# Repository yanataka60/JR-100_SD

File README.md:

# National JR-100にSD-CARDとのロード、セーブ機能

　JR-100でSD-CARDからPROG形式ファイルのロード、セーブ機能を実現するものです。

　CMTからの読み込み実行に数分掛かっていたゲームも数十秒で実行できます。

　接続は、JR-100本体後ろの拡張端子に直接挿して使います。

　なお、Arduino、ROM、GALへ書き込むための機器が別途必要となります。

　オプションとしてジョイスティックポート、拡張RAM($4000～$7FFF)も装備できます。

### 2025.2.26 PIOに6821を使ったRev2.1ではPIOアクセス時の画面ノイズが発生しないので6821版を正式版とし、8255版は8255フォルダに移動しました。なお、開発に使用した3台のJR-100では6821版、8255版ともに安定動作していますが、8255版は動作不安定であると報告された機体でも6821版は安定動作しているとの動作報告がありました。

## 回路図
　KiCadフォルダ内のJR-100_SD.pdfを参照してください。

[回路図](https://github.com/yanataka60/JR-100_SD/blob/main/Kicad/JR-100_SD.pdf)

## 部品
|番号|品名|数量|備考|
| ------------ | ------------ | ------------ | ------------ |
|J1(J2)|50Pカードエッジコネクタ|1|せんごくネット通販 HRS CR22A-50D-2.54DSなど|
|J4|コネクタ 2Pin|1|ピンヘッダで代用するときはGNDと間違えないよう1Pinで5Vだけにしたほうが良い|
|J5|DCジャック|1|秋月電子通商 MJ-179PHなど|
||J6、J7のいずれか|||
|J6|Micro_SD_Card_Kit|1|秋月電子通商 AE-microSD-LLCNV (注1) (注2)|
|J7|MicroSD Card Adapter|1|Arduino等に使われる5V電源に対応したもの (注2)|
|U1|GAL22V10|1||
|U3|ROM 2764/28C64相当品|1||
|U5|6821|1|若松通商 HD46821P等|
|U6|Arduino_Pro_Mini_5V|1|Atmega328版を使用 168版は不可。(注3)|
|C1,C2,C5|積層セラミックコンデンサ 0.1uF|3||
|C6|電解コンデンサ 16v100uF|1||
|S1|3Pスライドスイッチ|1|秋月電子通商 SS12D01G4など|
||ピンヘッダ|2Pin分|Arduino_Pro_MiniにはA4、A5用のピンヘッダが付いていないため別途調達が必要です 秋月電子通商 PH-1x40SGなど|
||ピンソケット(任意)|26Pin分|Arduino_Pro_Miniを取り外し可能としたい場合に調達します 秋月電子通商 FHU-1x42SGなど|

JR-100_SDに外部から電源を供給する場合
|番号|品名|数量|備考|
| ------------ | ------------ | ------------ | ------------ |
||ACアダプター 5V|1|秋月電子通商 M050200-A010JPなど|

RAM($4000～$7FFF)を拡張する場合
|番号|品名|数量|備考|
| ------------ | ------------ | ------------ | ------------ |
|U4|RAM 62256相当品|1||
|C3|積層セラミックコンデンサ 0.1uF|1||

ジョイスティックポートを付ける場合
|番号|品名|数量|備考|
| ------------ | ------------ | ------------ | ------------ |
|J3|D-SUB 9Pオス基板取付型|1|マルツ 3223DB9RP1S2など|
|U2|74LS366|1||
|C4|積層セラミックコンデンサ 0.1uF|1||
|R1-R5|10KΩ|5||

リセットスイッチを使う場合
|番号|品名|数量|備考|
| ------------ | ------------ | ------------ | ------------ |
|SW1|タクトスイッチ|1|秋月電子通商 DTS-63-N-Vなど|
|J8|コネクタ 1Pin|1|リセット用ご自分の環境に合わせてください|

　　　注1)秋月電子通商　AE-microSD-LLCNVのJ1ジャンパはショートしてください。

　　　注2)J6又はJ7のどちらかを選択して取り付けてください。

### 　　注3)Arduino Pro MiniはA4、A5ピンも使っています。

### MicroSD Card Adapterを使う
　J7に取り付けます。

　MicroSD Card Adapterについているピンヘッダを除去してハンダ付けするのが一番確実ですが、J4の穴にMicroSD Card Adapterをぴったりと押しつけ、裏から多めにハンダを流し込むことでハンダ付けをする方法もあります。なお、この方法の時にはしっかりハンダ付けが出来たかテスターで導通を確認しておいた方が安心です。

　ハンダ付けに自信のない方はJ2の秋月電子通商　AE-microSD-LLCNVをお使いください。AE-microSD-LLCNVならパワーLED、アクセスLEDが付いています。

## ROMへの書込み
　ROMフォルダ内のSD.binをROMライター(TL866II Plus等)を使って2764又は28C64に書き込みます。

　2764(8KByteROM)を使っていますが、JR-100_SDからアクセスされるのは4KByte分です。

## Arduinoプログラム
　Arduino IDEを使ってArduinoフォルダのJR-100_SDフォルダ内JR-100.inoを書き込みます。

　SdFatライブラリを使用しているのでArduino IDEメニューのライブラリの管理からライブラリマネージャを立ち上げて「SdFat」をインストールしてください。

　「SdFat」で検索すれば見つかります。「SdFat」と「SdFat - Adafruit Fork」が見つかりますが「SdFat」のほうを使っています。

注)Arduinoを基板に直付けしている場合、Arduinoプログラムを書き込むときは、JR-100本体とは接続を外し、GAL22V10を外したうえで書き込んでください。

## GALへの書込み
　Wincuplフォルダ内のJR100.jedをROMライター(TL866II Plus等)を使ってGAL22V10に書き込みます。

#### ~~2025.1.20 8255が正常にアクセスできない個体があると報告がありましたので修正しました。以前のプログラムで正常に動作していれば書き込み直す必要はありません。~~

## 接続
　JR-100本体後ろの拡張端子に挿し込みます。

.jpg)

## 電源の供給
　JR-100の拡張端子には+5Vが出ていないため、JR-100_SDには別途電源を供給する必要があります。

　私は純正の電源アダプタではなく、別に入手したスイッチング電源を使用しているため、内部電源として本体内の+5Vが供給されているピンから線を引き出してJR-100_SDに供給しています。

　純正の電源アダプタを使用している方が内部から+5Vを引き出し内部電源としてJR-100_SDへ供給する場合、もしかすると電力不足で誤動作するかもしれません。

　もし、動作異常が起こるようであれば別に5V電源アダプタを用意し、外部電源として供給してください。

#### 2025.1.20 純正の電源アダプタを借りて試したところ、内部から引き出した+5Vで問題なく動作しました。

## リセットスイッチ
　リセットスイッチはJ8コネクタに接続された信号線をGNDに落とすためだけのスイッチです。

　リセットスイッチとして利用するためには、本体内部からリセット用の信号線を引き出してくる必要があります。

　引き出し方についてはWeb等で調べてください。

## SD-CARD
　出来れば8GB以下のSDカードを用意してください。

　ArduinoのSdFatライブラリは、SD規格(最大2GB)、SDHC規格(2GB～32GB)に対応していますが、SDXC規格(32GB～2TB)には対応していません。

　また、SDHC規格のSDカードであっても32GB、16GBは相性により動作しないものがあるようです。

　FAT16又はFAT32が認識できます。NTFSは認識できません。

　ルートに置かれた拡張子が「.PRG」のPROG形式ファイルのみ認識できます。(PROG形式以外のファイル、フォルダも表示されますがLOADの対象になりません)

　ファイル名は「.PRG」を含めて31文字まで、ただし半角カタカナ、及び一部の記号はArduinoが認識しないので使えません。パソコンでファイル名を付けるときはアルファベット、数字および空白でファイル名をつけてください。

## PROG形式
　けむしろうさん作JR-100エミュレータver2で採用されているファイル形式です。

https://yorumomiji.sakura.ne.jp/contents/jr-100-emulator

　PROG形式の詳細については、ページ中ほどの「JR-100エミュレータver2ユーザーズガイド」から「ファイル形式」「PROG形式」を参照してください。

　ただし、現在公開されているJR-100エミュレータver2.4.0は、PROG形式フォーマットバージョン2が採用されておりフォーマットバージョン1と互換性がありません。

　JR-100_SDではフォーマットバージョン1に対応、フォーマットバージョン2は単一セクションのみのPRGファイル読み込みだけ対応しています。

#### 注)複数セクションが含まれるフォーマットバージョン2 PRGファイルは読み込ませないでください。最初のセクションの読込が終了した後、Arduinoは次のセクションを送出しようとして待機状態となり、電源を入れ直すか、RESETするまで正常に動作しなくなります。

　エミュレータで使う本体ROMデータはPROG形式フォーマットバージョン1で動作しますのでJR-100_SDからMSAVEすれば簡単に作成できます。

## 使い方

### JR-100_SDの準備
　JR-100を起動したらHCOPYコマンド(CTRL+B)を実行します。

　「JR-100_SD READY OK!」と表示されたらSD-CARDにアクセスできます。

　もう一度HCOPYコマンド(CTRL+B)を実行すると「CMT READY OK!」と表示されCMTに戻ります。

　HCOPYコマンド(CTRL+B)を実行する度にJR-100_SDとCMTが切り替わります。

### BASICコマンド

　~SDへのアクセス中に画面にノイズが出ますが、異常ではありません。ノイズが出ないようにする方法が不明なためそのままにしてあります。~(2025.2.20 PIOを6821にすることで解消されました。)

#### SDDIR[CR]又はSDDIR "文字列"[CR]
　SDDIR[CR]とするとSD-CARDルートディレクトリにあるファイルの一覧を表示します。

　SDDIR "文字列"[CR]とするとSD-CARDルートディレクトリにあるその文字列から始まるファイルの一覧を表示します。

　10件表示したところで指示待ちになるので打ち切るならRETURNを入力すると打ち切られ、Bキーで前の10件に戻ります。それ以外のキーで次の10件を表示します。

　LOADしたいファイルを見つけたら左端の数字のキーを押せばLOADされます。

　BASICプログラムか、機械語プログラムかは自動で判断します。

　表示される順番は、登録順となりファイル名アルファベッド順などのソートした順で表示することはできません。

#### LOAD "DOSファイル名"[CR]
　指定したDOSフィル名のプログラムをSD-CARDからLOADします。

　BASICプログラムか、機械語プログラムかは自動で判断し、どちらをLOADしているかメッセージに表示します。

　また、機械語プログラムのLOAD時には読み込み開始アドレス、読み込み終了アドレスも表示されます。

　MLOADコマンドは使えませんのでLOADコマンドを使用してください。

　ファイル名の最後の「.PRG」も有っても無くても構いません。

　例)

　　LOAD "TEST" -> DOSファイル名「TEST.PRG」を読み込みます。

　　LOAD "TEST.BAS" -> DOSファイル名「TEST.BAS.PRG」を読み込みます。

　　LOAD "TEST.BAS.CMT" -> DOSファイル名「TEST.BAS.PRG」を読み込みます。

#### MEXEC[CR]
　機械語プログラムをLOADした後、A=USR($xxxx)[CR]として機械語プログラムを実行する代わりに実行アドレスが読み込み開始アドレスと同じ場合にはMEXEC[CR]とすることで機械語プログラムを実行できます。

#### SAVE "DOSファイル名"[CR]
　BASICプログラムを指定したDOSフィル名でSD-CARDに上書きSAVEします。

　ファイル名の省略は出来ません。

　ファイル名の最後の「.PRG」は有っても無くても構いません。

　指定したDOSファイル名の最初の16文字がPROG形式の中に保存されるファイル名として使われます。

　BASICプログラムであることを識別するためDOSファイル名に「.BAS」を含ませることを推奨します。

　例)

　　SAVE "TEST" -> 「TEST.PRG」で保存される。

　　SAVE "TEST.BAS" -> 「TEST.BAS.PRG」で保存される。

#### MSAVE "DOSファイル名",$xxxx,$yyyy[CR]
　16進数4桁で指定する$xxxxから$yyyyまでの機械語プログラムを指定したDOSフィル名でSD-CARDに上書きSAVEします。

　ファイル名の省略は出来ません。

　ファイル名の最後の「.PRG」は有っても無くても構いません。

　指定したDOSファイル名の最初の16文字がPROG形式の中に保存されるファイル名として使われます。

　機械語プログラムであることを識別するためDOSファイル名に「.BIN」を含ませることを推奨します。

　例)

　　MSAVE "TEST",$E000,$FFFF -> 「TEST.PRG」で保存される。

　　MSAVE "TEST.BIN",$E000,$FFFF -> 「TEST.BIN.PRG」で保存される。

#### A=USR($DF00)[CR]【メモリテスト】
　RAMをテストします。

　アドレス$0246からエラーが発生するまでRAMに$55を書き込み、$55が読みだせるか、次に$AAを書き込み、$AAが読みだせるか、テストを行います。

　RAMにエラーが無い場合、拡張RAMを実装していなければ$4000、拡張RAMを実装していれば$8000でエラーとなり終了します。

　それ以外のアドレスで停止すればそのアドレスに問題があります。

#### A=USR($DE00,$xxxx)[CR]【メモリダンプ】
　16進数4桁で指定するアドレス$xxxxから64Byte分のメモリをダンプします。

　64Byte表示したところで指示待ちになるので次の64Byteを表示するならSPACEキー又はNキー、前の64Byteを表示するならBキー、それ以外のキーでBASICに戻ります。

#### A=USR($DD00,$xxxx)[CR]【メモリエディット】
　16進数4桁で指定するアドレス$xxxxからメモリに書き込みます。

　アドレス$xxxxを表示して指示待ちになるので書き込みたいデータを16進数で入力してください。

　止めたい時はRETURNキーを押せばBASICに戻ります。

## I/Oポートのデコードについて
　JR-100_SDにおいてジョイスティックポート、6821(8255)、拡張RAM、拡張ROMのアドレスデコードはすべてGAL22V10で行っていますが、ピン数の関係で16Bitすべてのアドレス線をデコードすることが出来ていません。

　拡張RAM、拡張ROMのアドレスデコードに問題はありませんが、ジョイスティックポート、6821(8255)は以下の扱いになります。

　ジョイスティックポート回路の参考にさせていただいた「にがMSX～JR-100用ジョイスティックインターフェイスの製作～」ではジョイスティックIOは$CC02となっていますが、JR-100_SDでは$CC00～$CC0Fのどこをアクセスしても同じ扱いです。

　6821(8255)はSDアクセスプログラム上$CC10～$CC13に配置されているとして記述していますが、$CC14～$CC1Fまでイメージが発生しています。

## ジョイスティック
　MSX用ジョイスティックが使用できます。

## 操作上の注意
　SD-CARDにアクセスしていない時には電源が入ったままでもSD-CARDを抜くことが出来ます。

　再度SD-CARDを挿入した後、SDDIR、LOAD、SAVE等でSD-CARDに3回ほどアクセスすれば復旧します。

　ただし、SD-CARDの抜き差しは電源を切った状態で行うほうがより確実です。

## 謝辞
　基板の作成に当たり以下のデータを使わせていただきました。ありがとうございました。

　　Arduino Pro Mini

　　　https://github.com/g200kg/kicad-lib-arduino

　　AE-microSD-LLCNV

　　　https://github.com/kuninet/PC-8001-SD-8kRAM

　けむしろう様、ファイルフォーマットにPROG形式を採用させていただきました。ありがとうございました。

　　https://asamomiji.jp/contents/jr-100%e3%82%a8%e3%83%9f%e3%83%a5%e3%83%ac%e3%83%bc%e3%82%bf%e7%b7%8f%e5%90%88

　にが様、ジョイスティックポートの回路図を参考に使わさせていただきました。ありがとうございました。

　　http://niga2.sytes.net/msx/JR100_3.html

　くりすと@kurist2010様、HCOPY(CTRL+B)を使ったらどうかという貴重な助言ありがとうございました。

## 追記
2025.1.9 複数セクションを含むフォーマットバージョン2 PRGファイルは扱えないことを追記しました。

2025.1.20 8255が正常にアクセスできない個体があるようなのでGAL22V10のプログラムを修正。SDDIRコマンドの後ろに空白が有ると文字列を認識しないバグを修正。

2025.1.24 動作不安定であるとの動作報告があったことを追記。

2025.1.31 ROMプログラムにJR-200_SD用プログラムをUPDATEしてしまったので元のプログラムを再UPDATE。2025.1.23の時点から修正なし。

2025.2.8 現時点での安定動作確認状況を追加。

2025.2.20 PIOに6821を採用した6821版に移行した。

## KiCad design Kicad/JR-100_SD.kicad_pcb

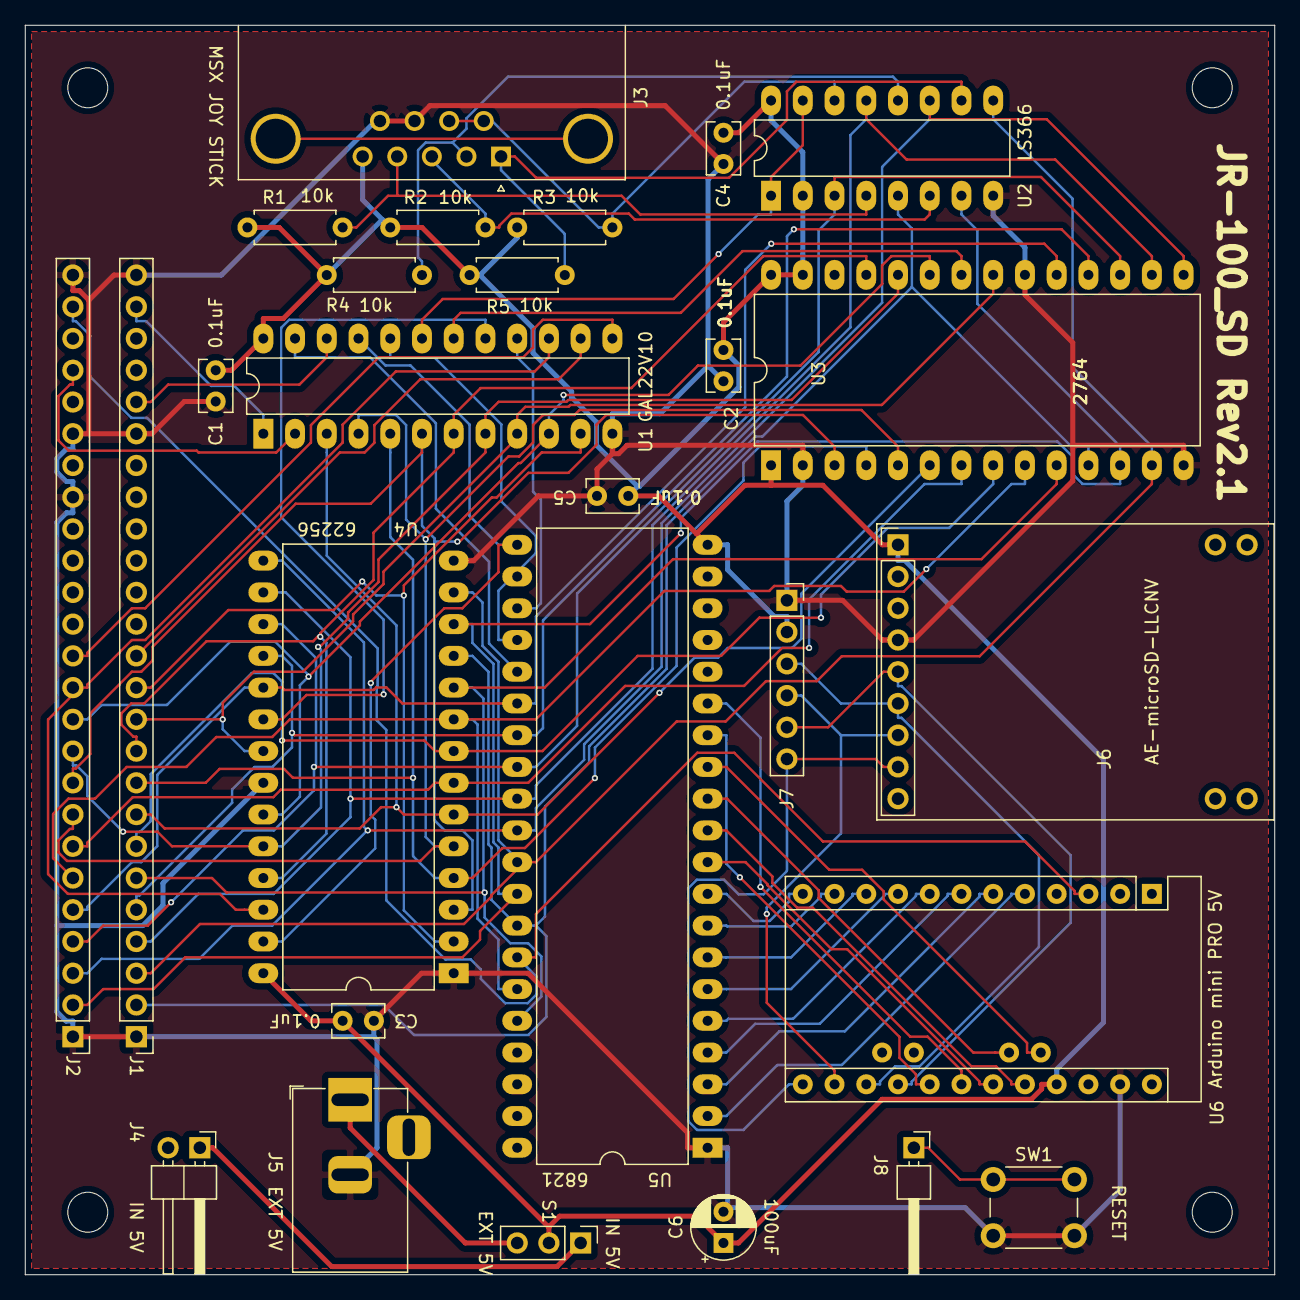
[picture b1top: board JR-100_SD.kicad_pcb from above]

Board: 2 copper layers, 100.0 x 100.0 mm, 31 parts (0 on the bottom side), 63 nets.

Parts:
C1, C2, C3, C4, C5: 0.1uF; C_Rect_L4.0mm_W2.5mm_P2.50mm
C6: 100uF; CP_Radial_D5.0mm_P2.50mm
J1, J2: Conn_01x25; PinHeader_1x25_P2.54mm_Vertical
J3: MSX JOY STICK; DSUB-9_Male_Horizontal_P2.77x2.84mm_EdgePinOffset7.70mm_Hou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
J4: IN 5V; PinHeader_1x02_P2.54mm_Horizontal
J5: EXT 5V; BarrelJack_Horizontal
J6: Micro_SD_Card_Kit; AE-microSD-LLCNV
J7: MicroSD Card Adapter; PinSocket_1x06_P2.54mm_Vertical
J8: Conn_01x01; PinHeader_1x01_P2.54mm_Horizontal
MH1, MH2, MH3, MH4: MountingHole_3.2mm_M3
R1, R2, R3, R4, R5: 10k; R_Axial_DIN0207_L6.3mm_D2.5mm_P7.62mm_Horizontal
S1: IN/EXT; PinHeader_1x03_P2.54mm_Vertical
SW1: SW_Push; SW_PUSH_6mm_H4.3mm
U1: GAL22V10; DIP-24_W7.62mm_LongPads
U2: 74LS366; DIP-16_W7.62mm_LongPads
U3: 2764; DIP-28_W15.24mm_LongPads
U4: 62256; DIP-28_W15.24mm_LongPads
U5: 6821; DIP-40_W15.24mm_LongPads
U6: Arduino_Pro_Mini_5V; Arduino_Pro_Mini

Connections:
+5V: C1.1, C2.1, C3.1, C4.2, C5.1, C6.1, J3.5, J6.1, J7.2, R1.1, R2.1, R3.1, R4.1, R5.1, S1.2, U1.24, U2.2, U2.16, U3.1, U3.27, U3.28, U4.28, U5.20, U6.21
/A0: J1.6, U3.10, U4.10, U5.36
/A1: J2.6, U3.9, U4.9, U5.35
/A2: J1.7, U3.8, U4.8
/A3: J2.7, U3.7, U4.7
/A4: J1.8, U1.3, U3.6, U4.6
/A5: J2.8, U1.4, U3.5, U4.5
/A6: J1.9, U1.5, U3.4, U4.4
/A7: J2.9, U1.6, U3.3, U4.3
/A8: J1.10, U1.7, U3.25, U4.25
/A9: J2.10, U1.8, U3.24, U4.24
/A10: J1.11, U1.9, U3.21, U4.21
/A11: J2.11, U1.10, U3.23, U4.23
/A12: J1.12, U1.11, U4.2
/A13: J2.12, U1.15, U4.26
/A14: J1.13, U1.14
/A15: J2.13, U1.13
/BKILL: J2.22, U1.2
/CLOCK: J1.24, U1.1
/CS: J6.8, J7.6, U6.13
/DB0: J1.2, U2.5, U3.11, U4.11, U5.33
/DB1: J2.2, U2.7, U3.12, U4.12, U5.32
/DB2: J1.3, U2.9, U3.13, U4.13, U5.31
/DB3: J2.3, U2.11, U3.15, U4.15, U5.30
/DB4: J1.4, U2.13, U3.16, U4.16, U5.29
/DB5: J2.4, U2.3, U3.17, U4.17, U5.28
/DB6: J1.5, U3.18, U4.18, U5.27
/DB7: J2.5, U3.19, U4.19, U5.26
/JOY: U1.19, U2.1, U2.15
/MISO: J6.6, J7.3, U6.15
/MOSI: J6.7, J7.4, U6.14
/PIO: U1.16, U5.23
/RAM: U1.17, U4.20
/ROM: U1.18, U3.22
/SCK: J6.5, J7.5, U6.16
/~CLOCK: U1.23, U5.25
/~PIO: U1.20, U5.22, U5.24
/~RD: J1.21, U1.22
/~RESET: J2.24, U5.34, U6.3
/~WE: U1.21, U4.27, U5.21
GND: C1.2, C2.2, C3.2, C4.1, C5.2, C6.2, J1.1, J1.20, J1.25, J2.1, J2.18, J2.20, J2.25, J3.8, J3.9, J5.2, J6.4, J7.1, SW1.2, U1.12, U2.8, U3.2, U3.14, U3.20, U4.1, U4.14, U4.22, U5.1, U6.23
unnamed: J3.1, R5.2, U2.10
unnamed: J3.2, R4.2, U2.12
unnamed: J3.3, R2.2, U2.6
unnamed: J3.4, R1.2, U2.4
unnamed: J3.6, J3.7, R3.2, U2.14
unnamed: J4.1, S1.1
unnamed: J5.1, S1.3
unnamed: J8.1, SW1.1
unnamed: U5.2, U6.5
unnamed: U5.3, U6.6
unnamed: U5.4, U6.7
unnamed: U5.5, U6.8
unnamed: U5.6, U6.9
unnamed: U5.7, U6.10
unnamed: U5.8, U6.11
unnamed: U5.9, U6.12
unnamed: U5.10, U6.19
unnamed: U5.11, U6.20
unnamed: U5.12, U6.A4
unnamed: U5.13, U6.A5
unnamed: U5.14, U6.17
unnamed: U5.15, U6.18
